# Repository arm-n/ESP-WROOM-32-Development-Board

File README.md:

# ESP-WROOM-32 KiCad Prototype

A hardware prototyping project based on the ESP-WROOM-32 module, designed using KiCad. This repository contains the circuit schematic, PCB layout, Gerber manufacturing files, design screenshots, datasheets and supporting documentation.

The project was developed as a learning and hardware prototyping exercise, using technical documentation and component datasheets as references.

## Project Overview

| Parameter | Details |
|---|---|
| Project Name | ESP-WROOM-32 KiCad Prototype |
| Microcontroller Module | ESP-WROOM-32 |
| Design Software | KiCad |
| Project Type | Hardware / PCB Design |
| Design Stage | Prototype |
| Repository | ESP-WROOM-32-Development-Board |
| Author | Armaan |

## Repository Structure

```text
esp-wroom-32/
│
├── esp_wroom_32.kicad_pro       # KiCad project settings
├── esp_wroom_32.kicad_sch       # Circuit schematic
├── esp_wroom_32.kicad_pcb       # PCB layout
│
├── ESP-WROOM-32.PDF             # ESP-WROOM-32 datasheet
├── DRC.rpt                      # Design rule check report
│
├── gerber/                      # PCB manufacturing files
│   ├── esp_wroom_32-B_Cu.gbr
│   ├── esp_wroom_32-F_Cu.gbr
│   ├── esp_wroom_32-B_Mask.gbr
│   ├── esp_wroom_32-F_Mask.gbr
│   ├── esp_wroom_32-B_Paste.gbr
│   ├── esp_wroom_32-F_Paste.gbr
│   ├── esp_wroom_32-B_Silkscreen.gbr
│   ├── esp_wroom_32-F_Silkscreen.gbr
│   ├── esp_wroom_32-Edge_Cuts.gbr
│   ├── esp_wroom_32-NPTH.drl
│   ├── esp_wroom_32-PTH.drl
│   └── esp_wroom_32-job.gbrjob
│
├── images/                      # Design screenshots
│   └── *.png
│
├── README.md                    # Project documentation
└── LICENSE                      # Licence, if applicable
```

## Hardware Design

This project uses the ESP-WROOM-32 module, which provides integrated Wi-Fi and Bluetooth connectivity.

The KiCad project includes the following design files and documentation:

- **Schematic:** Circuit diagram and electrical connections.
- **PCB Layout:** Component placement, copper routing and board layout.
- **Gerber Files:** PCB fabrication outputs.
- **DRC Report:** Design rule check results from the saved design.
- **Datasheet:** Technical specifications and reference information for the ESP-WROOM-32 module.
- **Design Images:** Screenshots documenting the schematic, PCB and design process.

Refer to the KiCad schematic and PCB files for the actual circuit implementation and board layout.

## Tools and Software

The following tools and resources are used in this project:

- [KiCad](https://www.kicad.org/) — Electronic schematic capture and PCB design.
- [Git](https://git-scm.com/) — Version control.
- [GitHub](https://github.com/) — Project hosting and version management.
- [Espressif Documentation](https://www.espressif.com/) — Technical documentation and component specifications.

## Getting Started

### 1. Clone the Repository

Clone the project from GitHub using:

```bash
git clone https://github.com/arm-n/ESP-WROOM-32-Development-Board.git
```

Navigate to the project directory:

```bash
cd ESP-WROOM-32-Development-Board
```

### 2. Open the KiCad Project

1. Install and launch KiCad.
2. Open the KiCad Project Manager.
3. Select **File → Open Project**.
4. Navigate to the cloned repository.
5. Open `esp_wroom_32.kicad_pro`.

### 3. Explore the Design

**Schematic**

Open the schematic editor to inspect the circuit diagram, components and electrical connections.

**PCB Layout**

Open the PCB editor to examine component placement, copper routing, board outline and PCB design.

**Design Rule Check**

The repository includes a `DRC.rpt` file containing the design rule check results from the time it was generated.

Run a fresh Design Rule Check (DRC) in KiCad before modifying, fabricating or using the PCB.

## PCB Manufacturing Files

The `gerber/` directory contains the PCB fabrication files generated from the KiCad PCB layout.

| File | Description |
|---|---|
| `F_Cu.gbr` | Front copper layer |
| `B_Cu.gbr` | Back copper layer |
| `F_Mask.gbr` | Front solder mask |
| `B_Mask.gbr` | Back solder mask |
| `F_Paste.gbr` | Front solder paste |
| `B_Paste.gbr` | Back solder paste |
| `F_Silkscreen.gbr` | Front silkscreen |
| `B_Silkscreen.gbr` | Back silkscreen |
| `Edge_Cuts.gbr` | PCB board outline |
| `PTH.drl` | Plated through-hole drill file |
| `NPTH.drl` | Non-plated through-hole drill file |
| `job.gbrjob` | Gerber job configuration |

### Manufacturing Considerations

Before submitting the PCB for fabrication:

1. Verify the schematic and PCB layout.
2. Run the latest Electrical Rules Check (ERC) and Design Rules Check (DRC).
3. Inspect component footprints, placement and routing.
4. Verify the board outline and dimensions.
5. Inspect the Gerber files using a Gerber viewer.
6. Confirm that the drill files and fabrication outputs correspond to the latest PCB revision.
7. Check the fabrication requirements of the selected PCB manufacturer.

**Note:** The included manufacturing files represent a saved design revision. Verify them before ordering a PCB, as they may not reflect subsequent design changes.

## Design References

This project was developed using publicly available technical documentation and component datasheets for learning and design reference.

### Datasheets

- [ESP-WROOM-32 Datasheet — Espressif](https://documentation.espressif.com/esp32-wroom-32_datasheet_en.pdf)
- [ESP32 Datasheet — Espressif](https://documentation.espressif.com/esp32_datasheet_en.pdf)

These documents provide technical specifications, electrical characteristics, pin information and other reference material relevant to the ESP32 platform.

Third-party documentation, designs, images and other materials retain their respective copyrights and licences.

## Design Status

**Current Status: Prototype**

The repository contains the KiCad project files, schematic, PCB layout, Gerber manufacturing outputs, DRC report, datasheet and design screenshots.

The project is intended for educational purposes, hardware experimentation and PCB design practice.

Further review and validation are required before fabrication or use in a production application.

## Licence

The licensing of this project is subject to the ownership and permissions applicable to its individual design contributions and included third-party materials.

The **CERN Open Hardware Licence Version 2 — Permissive (CERN-OHL-P-2.0)** is a potential licence for original hardware design contributions, provided the contributor has the necessary rights to distribute them under its terms.

Third-party materials, including any incorporated reference designs, schematics, PCB layouts, symbols, footprints, images and documentation, remain subject to their respective copyrights and licences.

Attribution alone does not grant permission to redistribute or relicense third-party material.

Refer to the `LICENSE` file, if included, for the applicable licence terms.

## Author

**Armaan**

Hardware prototyping, KiCad schematic design and PCB development.

## Disclaimer

This project is provided for educational, experimental and hardware prototyping purposes.

The design and associated manufacturing files are provided without a guarantee of fitness for a particular purpose.

Users should independently verify the circuit, component specifications, electrical characteristics, PCB layout, manufacturing outputs and safety requirements before fabrication or use.

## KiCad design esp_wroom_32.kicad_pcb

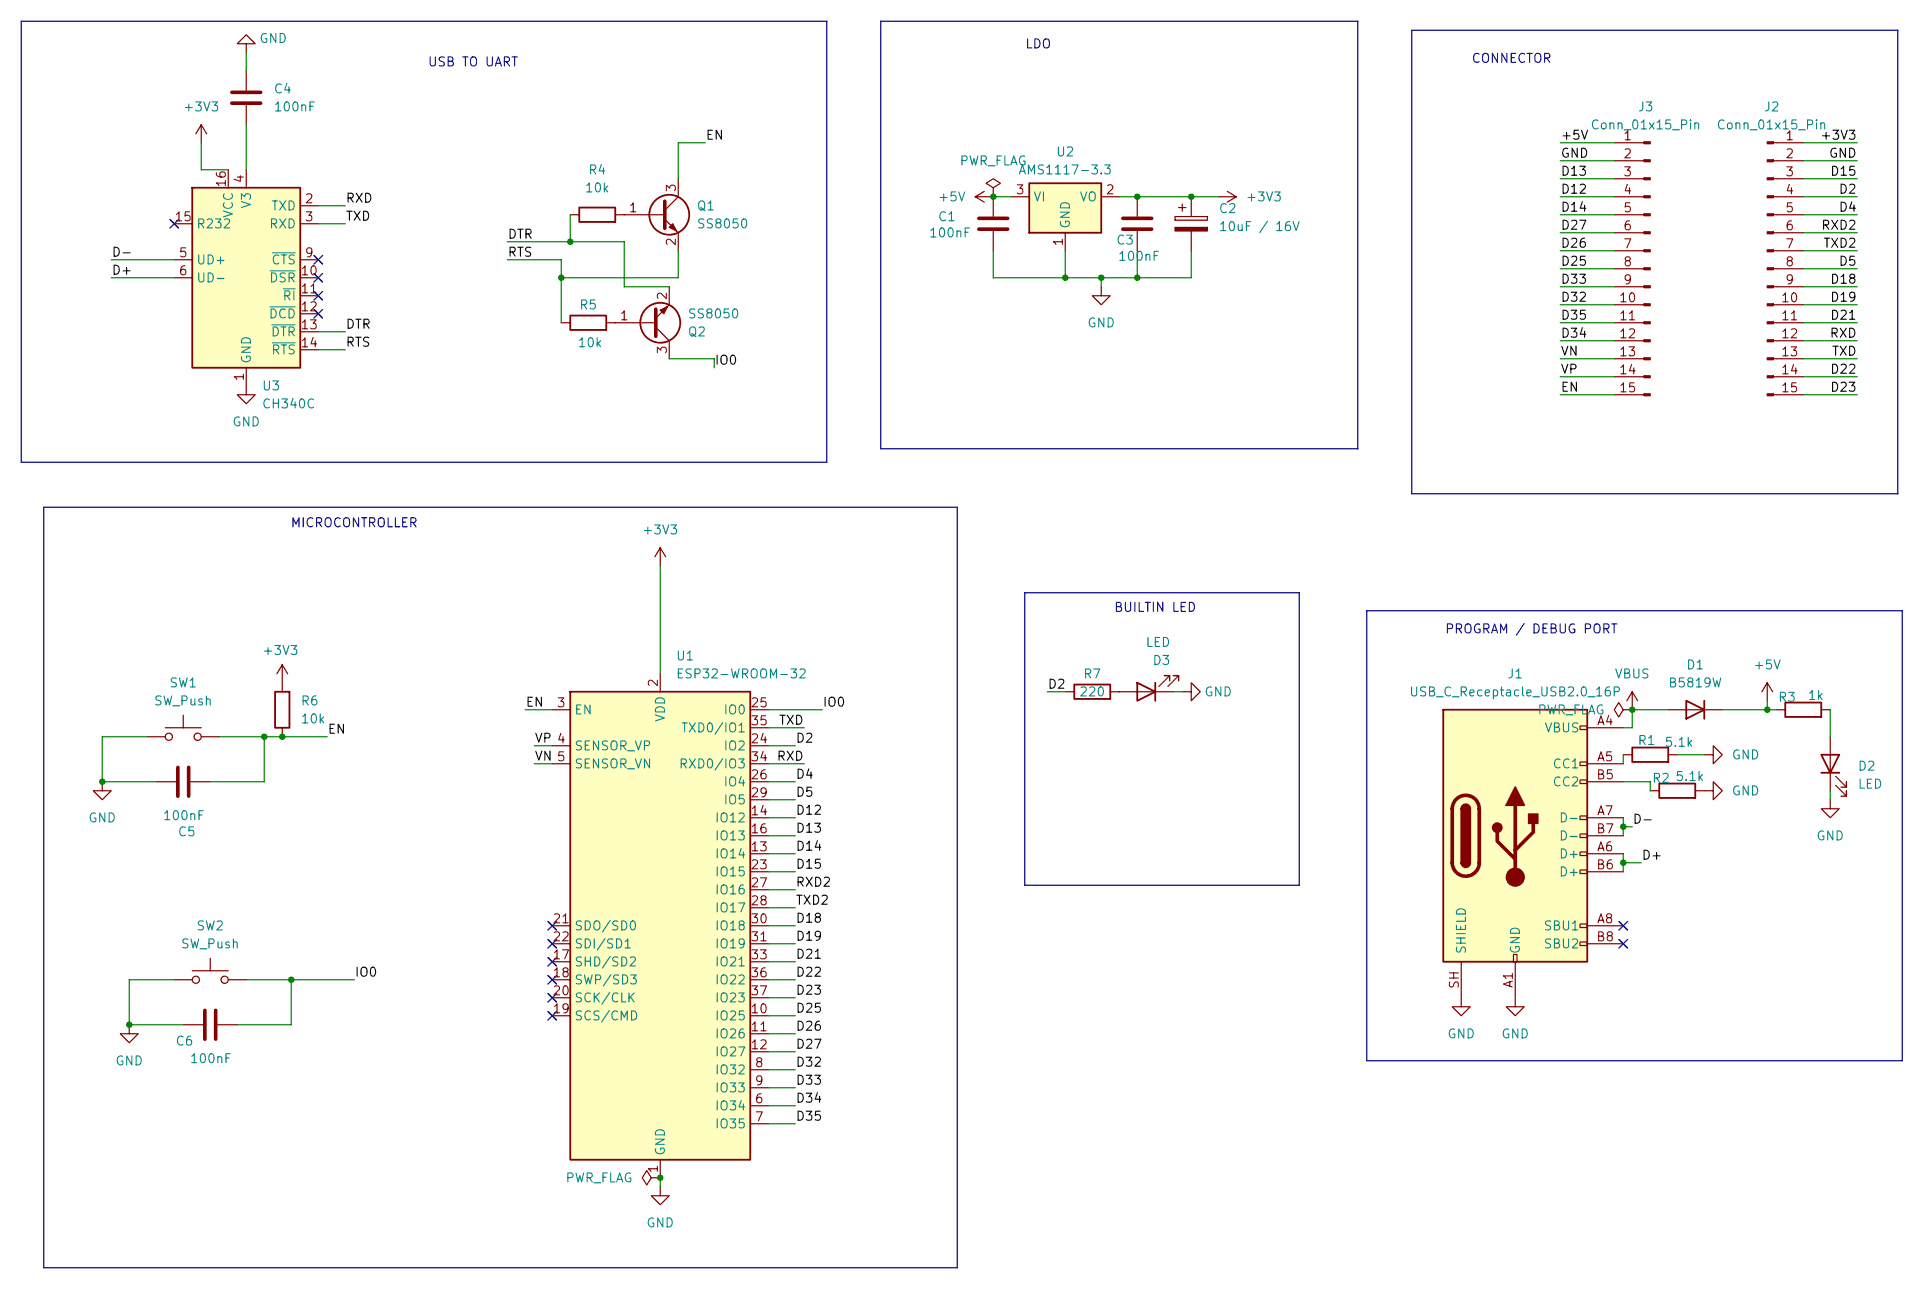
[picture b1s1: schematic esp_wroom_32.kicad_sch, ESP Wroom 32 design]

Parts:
C1, C3, C4, C5, C6: 100nF; C_0402_1005Metric
C2: 10uF / 16V; CP_EIA-3216-10_Kemet-I
D1: B5819W; D_SOD-123
D2, D3: LED; LED_0201_0603Metric
J1: USB_C_Receptacle_USB2.0_16P; USB_C_Receptacle_HRO_TYPE-C-31-M-12
J2, J3: Conn_01x15_Pin; PinSocket_1x15_P2.54mm_Vertical
Q1, Q2: SS8050; SOT-23
R1, R2: 5.1k; R_0603_1608Metric
R3: 1k; R_0603_1608Metric
R4, R5, R6: 10k; R_0603_1608Metric
R7: 220; R_0603_1608Metric
SW1, SW2: SW_Push; SW_Push_SPST_NO_Alps_SKRK
U1: ESP32-WROOM-32
U2: AMS1117-3.3; SOT-223-3_TabPin2
U3: CH340C; SOIC-16_3.9x9.9mm_P1.27mm

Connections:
+3V3: C2.1, C3.1, J2.1, R6.2, U1.2 (VDD), U2.2 (VO), U3.16 (VCC)
+5V: C1.1, D1.1 (K), J3.1, R3.1, U2.3 (VI)
/D2: J2.4, R7.1, U1.24 (IO2)
/D4: J2.5, U1.26 (IO4)
/D5: J2.8, U1.29 (IO5)
/D12: J3.4, U1.14 (IO12)
/D13: J3.3, U1.16 (IO13)
/D14: J3.5, U1.13 (IO14)
/D15: J2.3, U1.23 (IO15)
/D18: J2.9, U1.30 (IO18)
/D19: J2.10, U1.31 (IO19)
/D21: J2.11, U1.33 (IO21)
/D22: J2.14, U1.36 (IO22)
/D23: J2.15, U1.37 (IO23)
/D25: J3.8, U1.10 (IO25)
/D26: J3.7, U1.11 (IO26)
/D27: J3.6, U1.12 (IO27)
/D32: J3.10, U1.8 (IO32)
/D33: J3.9, U1.9 (IO33)
/D34: J3.12, U1.6 (IO34)
/D35: J3.11, U1.7 (IO35)
/D+: J1.A6 (D+), J1.B6 (D+), U3.6 (UD-)
/D-: J1.A7 (D-), J1.B7 (D-), U3.5 (UD+)
/DTR: Q2.2 (E), R4.1, U3.13 (~DTR)
/EN: C5.2, J3.15, Q1.3 (C), R6.1, SW1.2, U1.3 (EN)
/IO0: C6.2, Q2.3 (C), SW2.2, U1.25 (IO0)
/RTS: Q1.2 (E), R5.1, U3.14 (~RTS)
/RXD: J2.12, U1.34 (RXD0/IO3), U3.2 (TXD)
/RXD2: J2.6, U1.27 (IO16)
/TXD: J2.13, U1.35 (TXD0/IO1), U3.3 (RXD)
/TXD2: J2.7, U1.28 (IO17)
/VN: J3.13, U1.5 (SENSOR_VN)
/VP: J3.14, U1.4 (SENSOR_VP)
GND: C1.2, C2.2, C3.2, C4.2, C5.1, C6.1, D2.1 (K), D3.1 (K), J1.A1 (GND), J1.A12 (GND), J1.B1 (GND), J1.B12 (GND), J1.SH (SHIELD), J2.2, J3.2, R1.2, R2.2, SW1.1, SW2.1, U1.1 (GND), U1.15 (GND), U1.38 (GND), U1.39 (GND), U2.1 (GND), U3.1 (GND)
unnamed: D2.2 (A), R3.2
unnamed: D3.2 (A), R7.2
unnamed: J1.A5 (CC1), R1.1
unnamed: J1.B5 (CC2), R2.1
unnamed: Q1.1 (B), R4.2
unnamed: Q2.1 (B), R5.2
unnamed: C4.1, U3.4 (V3)
VBUS: D1.2 (A), J1.A4 (VBUS), J1.A9 (VBUS), J1.B4 (VBUS), J1.B9 (VBUS)

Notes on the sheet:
LDO
PROGRAM / DEBUG PORT
BUILTIN LED
CONNECTOR
USB TO UART
MICROCONTROLLER

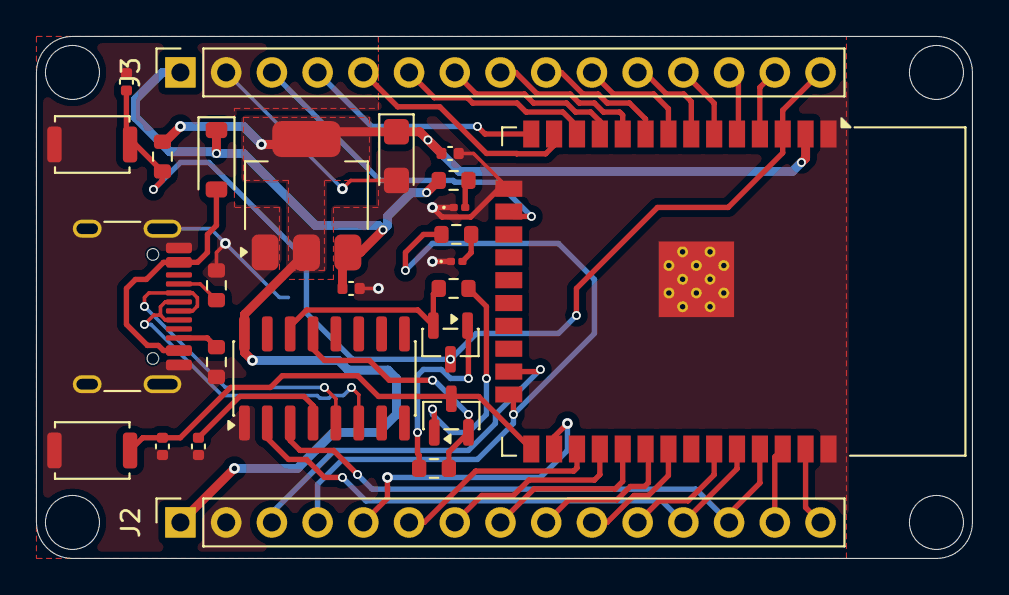
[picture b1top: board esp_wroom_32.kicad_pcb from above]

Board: 2 copper layers, 52.0 x 29.0 mm, 26 parts (0 on the bottom side), 42 nets.
